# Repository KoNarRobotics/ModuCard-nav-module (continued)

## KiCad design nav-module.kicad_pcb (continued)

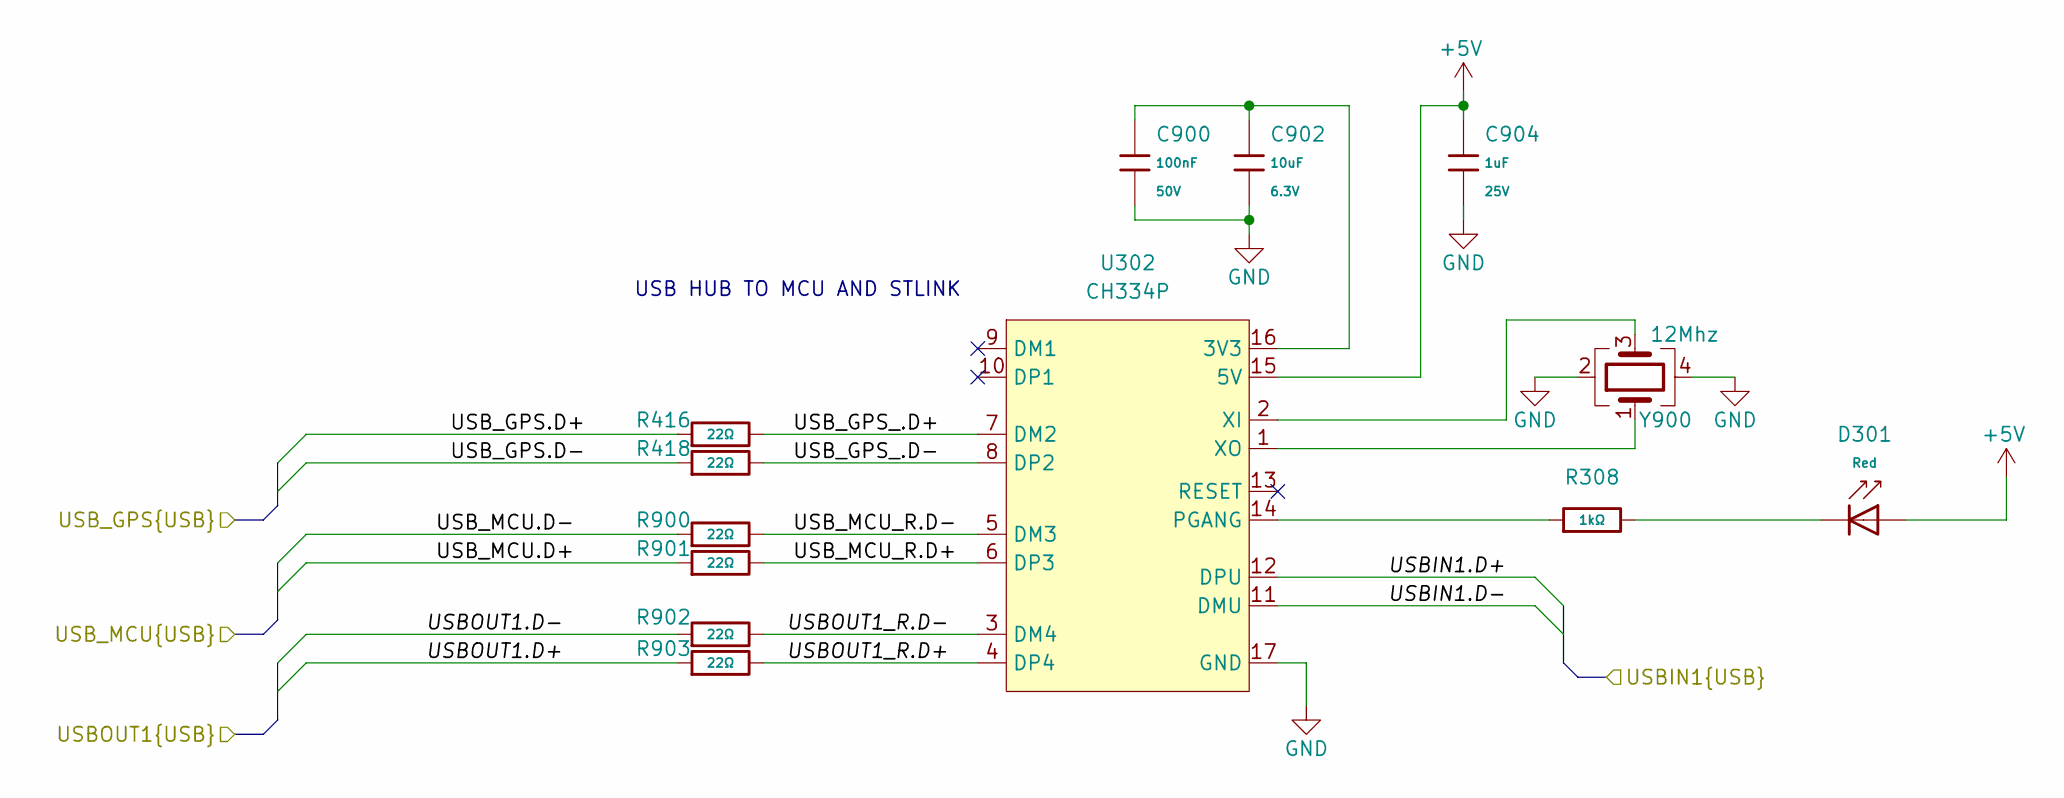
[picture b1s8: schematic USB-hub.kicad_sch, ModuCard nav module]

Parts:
C900: 100nF; C_0402; Voltage Rated 50V; Tolerance ±10%; Part CL05B104KB54PNC; LCSC C307331
C902: 10uF; C_0402; Voltage Rated 6.3V; Tolerance ±20%; Part CL05A106MQ5NUNC; LCSC C15525
C904: 1uF; C_0402; Voltage Rated 25V; Tolerance ±10%; Part CL05A105KA5NQNC; LCSC C52923
D301: Red; D_0603; Part KT-0603R; LCSC C2286
R308: 1kΩ; R_0402; Overload Voltage (Max) 50V; Tolerance ±1%; Part 0402WGF1001TCE; LCSC C11702
R416, R418, R900, R901, R902, R903: 22Ω; R_0402; Overload Voltage (Max) 50V; Tolerance ±1%; Part 0402WGF220JTCE; LCSC C25092
U302: CH334P; QFN-16-1EP_3x3mm_P0.5mm_EP1.7x1.7mm
Y900: 12Mhz; Crystal_SMD_3225-4Pin_3.2x2.5mm

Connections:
+5V: C904.1, D301.2, U302.15 (5V); also elsewhere on the board
/GPS-RTK/USB_GPS.D+: R416.1; also elsewhere on the board
/GPS-RTK/USB_GPS.D-: R418.1; also elsewhere on the board
/MCU/USB_MCU.D+: R901.1; also elsewhere on the board
/MCU/USB_MCU.D-: R900.1; also elsewhere on the board
/ST-LINK/ST-LINK.D+: R903.1; also elsewhere on the board
/ST-LINK/ST-LINK.D-: R902.1; also elsewhere on the board
/USB-hub/USBIN1.D+: U302.12 (DPU); also elsewhere on the board
/USB-hub/USBIN1.D-: U302.11 (DMU); also elsewhere on the board
/USB-hub/USBOUT1_R.D+: R903.2, U302.4 (DP4)
/USB-hub/USBOUT1_R.D-: R902.2, U302.3 (DM4)
/USB-hub/USB_GPS_.D+: R416.2, U302.7 (DM2)
/USB-hub/USB_GPS_.D-: R418.2, U302.8 (DP2)
/USB-hub/USB_MCU_R.D+: R901.2, U302.6 (DP3)
/USB-hub/USB_MCU_R.D-: R900.2, U302.5 (DM3)
GND: C900.2, C902.2, C904.2, U302.17 (GND), Y900.2, Y900.4; also elsewhere on the board
unnamed: D301.1, R308.2
unnamed: C900.1, C902.1, U302.16 (3V3)
unnamed: R308.1, U302.14 (PGANG)
unnamed: U302.2 (XI), Y900.3
unnamed: U302.1 (XO), Y900.1

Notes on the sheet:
USB HUB TO MCU AND STLINK

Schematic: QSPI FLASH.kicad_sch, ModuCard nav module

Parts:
C100: 100nF; C_0402; Voltage Rated 50V; Tolerance ±10%; Part CL05B104KB54PNC; LCSC C307331
U100: W25Q128; SOIC-8_L5.3-W5.3-P1.27-LS8.0-BL; Part W25Q128JVSIQ; LCSC C97521

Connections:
+3V3: C100.1, U100.8 (VCC); also elsewhere on the board
/MCU/QSPI1.CS: U100.1 (CS#); also elsewhere on the board
/MCU/QSPI1.IO0: U100.5 (DI); also elsewhere on the board
/MCU/QSPI1.IO1: U100.2 (DO); also elsewhere on the board
/MCU/QSPI1.IO2: U100.3 (IO2); also elsewhere on the board
/MCU/QSPI1.IO3: U100.7 (IO3); also elsewhere on the board
/MCU/QSPI1.SCLK: U100.6 (CLK); also elsewhere on the board
GND: C100.2, U100.4 (GND); also elsewhere on the board

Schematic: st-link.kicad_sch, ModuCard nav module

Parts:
C700: 1uF; C_0402; Voltage Rated 25V; Tolerance ±10%; Part CL05A105KA5NQNC; LCSC C52923
C701, C702, C703, C704, C705, C706: 100nF; C_0402; Voltage Rated 50V; Tolerance ±10%; Part CL05B104KB54PNC; LCSC C307331
C707, C708: 33pF; C_0402; Voltage Rated 50V; Tolerance ±5%; Part 0402CG330J500NT; LCSC C1562
D700: Blue; D_0603; Part 19-217/BHC-ZL1M2RY/6T; LCSC C2986058
D701: Green; D_0603; Part 19-217/GHC-YR1S2/6T; LCSC C2986059
Q700: MMST3904; Q_SOT-323; Part MMST3904; LCSC C22388837
R700, R702: 100kΩ; R_0402; Overload Voltage (Max) 50V; Tolerance ±1%; Part 0402WGF1003TCE; LCSC C25741
R701, R703, R705, R707, R709, R713: 10kΩ; R_0402; Overload Voltage (Max) 50V; Tolerance ±1%; Part 0402WGF1002TCE; LCSC C25744
R704, R708, R715, R716: 22Ω; R_0402; Overload Voltage (Max) 50V; Tolerance ±1%; Part 0402WGF220JTCE; LCSC C25092
R706: 10kΩ; R_0402; Overload Voltage (Max) 50V; Tolerance ±1%; Part 0402WGF1002TCE; LCSC C25744; not fitted
R710, R714: 100Ω; R_0402; Overload Voltage (Max) 50V; Tolerance ±1%; Part 0402WGF1000TCE; LCSC C25076
R711: 39kΩ; R_0402; Overload Voltage (Max) 50V; Tolerance ±1%; Part 0402WGF3902TCE; LCSC C25783
R712: 1.2kΩ; R_0402; Overload Voltage (Max) 50V; Tolerance ±1%; Part 0402WGF1201TCE; LCSC C25862
TP700, TP701: TestPoint; TestPoint_Pad_D1.0mm
TP702, TP703, TP704, TP705, TP706: TestPoint_Pad_D1.0mm
U700: STM32F103CBTx; LQFP-48_7x7mm_P0.5mm
Y700: 8 MHz; CRYSTAL-SMD_4P-L3.2-W2.5-BL

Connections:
+3V3: C700.1, C701.1, C702.1, C703.1, C704.1, C705.1, Q700.3 (C), R700.1, R701.1, R707.1, TP702.1, U700.1 (VBAT), U700.9 (VDDA), U700.24 (VDD), U700.36 (VDD), U700.48 (VDD); also elsewhere on the board
+5V: R709.1; also elsewhere on the board
/MCU/SWD.SWCLK: R704.2, R715.1; also elsewhere on the board
/MCU/SWD.SWDIO: R716.1; also elsewhere on the board
/MCU/SWD.~RST: R708.1; also elsewhere on the board
/ST-LINK/CLK: TP705.1, U700.37 (PA14)
/ST-LINK/DIO: TP704.1, U700.34 (PA13)
/ST-LINK/LED: D700.1, D701.2, U700.30 (PA9)
/ST-LINK/ST-LINK.D+: R712.2, U700.33 (PA12); also elsewhere on the board
/ST-LINK/ST-LINK.D-: U700.32 (PA11); also elsewhere on the board
/ST-LINK/STLINK-BOOT0: R702.2, TP703.1, U700.44 (BOOT0)
/ST-LINK/STLINK-OSC_IN: C707.1, U700.5 (PD0), Y700.1
/ST-LINK/STLINK-OSC_OUT: C708.1, U700.6 (PD1), Y700.3
/ST-LINK/STLINK-RST: C706.1, R700.2, U700.7 (NRST)
/ST-LINK/STLINK_RX: TP701.1, U700.13 (PA3)
/ST-LINK/STLINK_TX: TP700.1, U700.12 (PA2)
/ST-LINK/SWO: U700.31 (PA10)
/ST-LINK/USB_RENUM: R710.2, U700.38 (PA15)
GND: C700.2, C701.2, C702.2, C703.2, C704.2, C705.2, C706.2, C707.2, C708.2, R702.1, R703.2, R705.1, R706.1, R711.2, R713.2, TP706.1, U700.8 (VSSA), U700.23 (VSS), U700.35 (VSS), U700.47 (VSS), Y700.2, Y700.4; also elsewhere on the board
unnamed: D700.2, R707.2
unnamed: D701.1, R713.1
unnamed: Q700.1 (B), R709.2, R710.1, R711.1
unnamed: Q700.2 (E), R712.1
unnamed: R701.2, R703.1, U700.10 (PA0)
unnamed: R704.1, U700.15 (PA5)
unnamed: R708.2, U700.18 (PB0)
unnamed: R714.2, U700.25 (PB12)
unnamed: R715.2, U700.26 (PB13)
unnamed: R714.1, R716.2, U700.27 (PB14)
unnamed: R705.2, U700.2 (PC13)
unnamed: R706.2, U700.3 (PC14)

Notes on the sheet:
Alternative GD32F103CB
SWD
NOTICE:
C707=C708 = (CL - 4pF) * 2
Monitor voltage rail 3V3 instead of target MCU voltage
https://stm32world.com/wiki/DIY_STM32_Programmer_(ST-Link/V2-1)
CAUTION:
Populate with STM32F103C8, STM32F103CB
Should be 1k5, but we try 1k2 because it is in basic parts
ACTIVITY LED
for providing amazing reverse engeenering of ST-link
MANDATORY CB VERSION
FORCE RENUMERATION OF USB DEVICES
https://github.com/lbthomsen/st-link/tree/master
Credit to:

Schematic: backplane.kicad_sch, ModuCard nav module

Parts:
J200: 09031967921; DIN41612_R_3x32_Female_Horizontal_THT; PARTREV D
U200: PESD5V0S2BT; SOT-23

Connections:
+5V_STDBY: J200.a3, J200.b3, J200.c3
+12V: J200.a11, J200.a12, J200.b11, J200.b12, J200.c11, J200.c12; also elsewhere on the board
+24V: J200.a14, J200.b14, J200.c14
/Backplane/BACKPLANE.D+: J200.a2, U200.2; also elsewhere on the board
/Backplane/BACKPLANE.D-: J200.c2, U200.1; also elsewhere on the board
/Backplane/CAN1.+: J200.a5, J200.b5, J200.c5; also elsewhere on the board
/Backplane/CAN1.-: J200.a6, J200.b6, J200.c6; also elsewhere on the board
/Backplane/CAN2.+: J200.a8, J200.b8, J200.c8; also elsewhere on the board
/Backplane/CAN2.-: J200.a9, J200.b9, J200.c9; also elsewhere on the board
/Backplane/GPIOC0: J200.b16
/Backplane/GPIOC1: J200.b17
/Backplane/GPIOC2: J200.b18
/Backplane/GPIOC3: J200.b19
/Backplane/GPIOC4: J200.b20
/Backplane/GPIOC5: J200.b21
/Backplane/GPIOC6: J200.b22
/Backplane/GPIOC7: J200.b23
/Backplane/GPIOC8: J200.b24
/Backplane/GPIOC9: J200.b25
/Backplane/GPIOC10: J200.b26
/Backplane/GPIOC11: J200.b27
/Backplane/GPIOC12: J200.b28
/Backplane/GPIOC13: J200.b29
/Backplane/GPIOC14: J200.b30
/Backplane/GPIOC15: J200.b31
/Backplane/GPIOL0: J200.a16
/Backplane/GPIOL1: J200.a17
/Backplane/GPIOL2: J200.a18
/Backplane/GPIOL3: J200.a19
/Backplane/GPIOL4: J200.a20
/Backplane/GPIOL5: J200.a21
/Backplane/GPIOL6: J200.a22
/Backplane/GPIOL7: J200.a23
/Backplane/GPIOL8: J200.a24
/Backplane/GPIOL9: J200.a25
/Backplane/GPIOL10: J200.a26
/Backplane/GPIOL11: J200.a27
/Backplane/GPIOL12: J200.a28
/Backplane/GPIOL13: J200.a29
/Backplane/GPIOL14: J200.a30
/Backplane/GPIOL15: J200.a31
/Backplane/GPIOR0: J200.c16
/Backplane/GPIOR1: J200.c17
/Backplane/GPIOR2: J200.c18
/Backplane/GPIOR3: J200.c19
/Backplane/GPIOR4: J200.c20
/Backplane/GPIOR5: J200.c21
/Backplane/GPIOR6: J200.c22
/Backplane/GPIOR7: J200.c23
/Backplane/GPIOR8: J200.c24
/Backplane/GPIOR9: J200.c25
/Backplane/GPIOR10: J200.c26
/Backplane/GPIOR11: J200.c27
/Backplane/GPIOR12: J200.c28
/Backplane/GPIOR13: J200.c29
/Backplane/GPIOR14: J200.c30
/Backplane/GPIOR15: J200.c31
GND: J200.a1, J200.a4, J200.a7, J200.a10, J200.a13, J200.a15, J200.a32, J200.b1, J200.b2, J200.b4, J200.b7, J200.b10, J200.b13, J200.b15, J200.b32, J200.c1, J200.c4, J200.c7, J200.c10, J200.c13, J200.c15, J200.c32, U200.3; also elsewhere on the board

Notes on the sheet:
USB
CAN
POWER FLAGS
USB

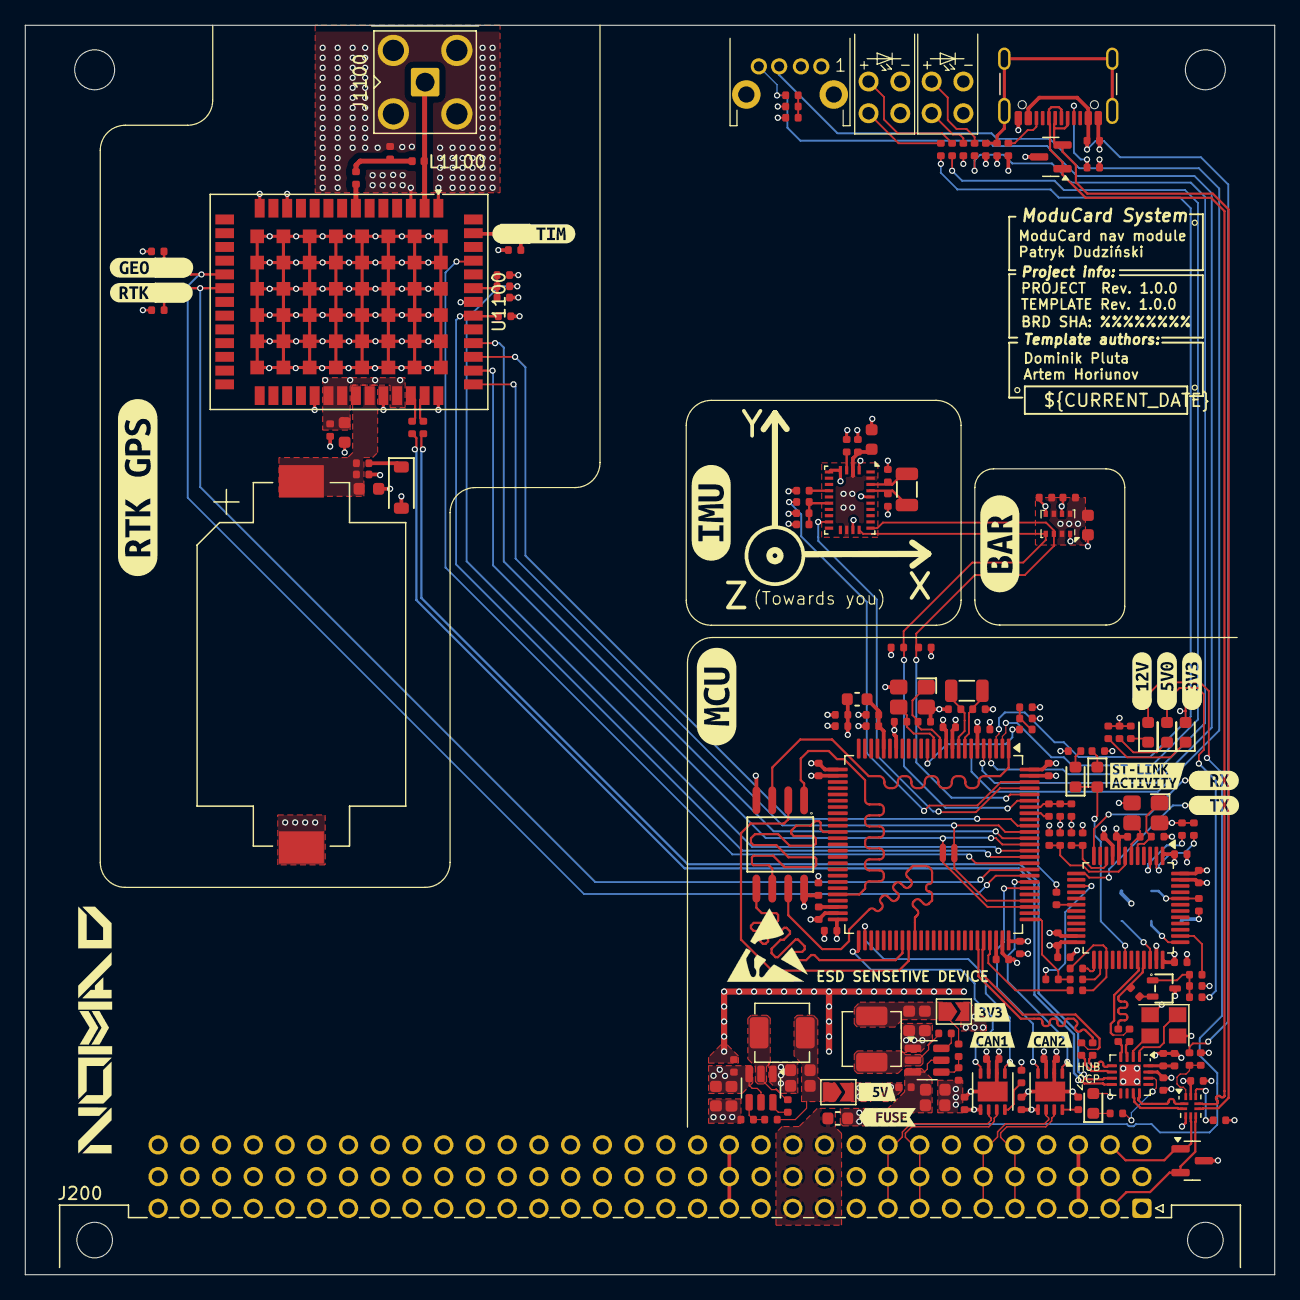
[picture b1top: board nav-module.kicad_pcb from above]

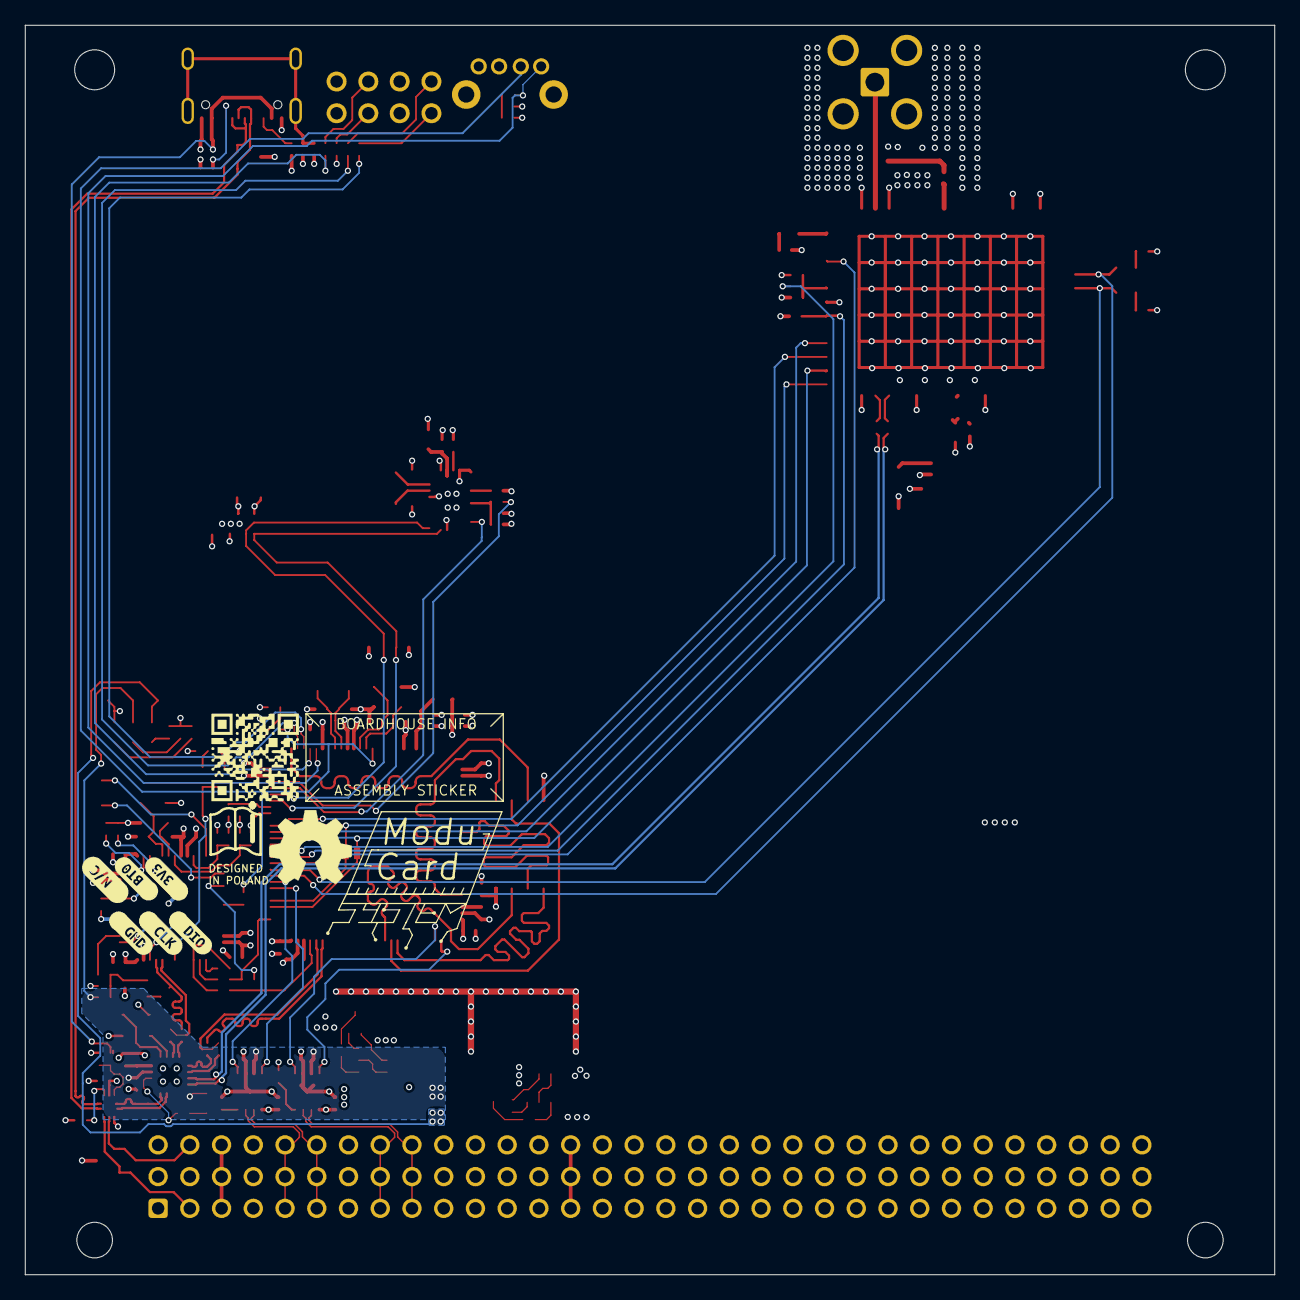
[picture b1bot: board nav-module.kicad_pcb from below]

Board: 4 copper layers, 100.0 x 100.0 mm, 208 parts (11 on the bottom side), 137 nets.

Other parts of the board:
kibuzzard-67B20BD5: G***; kibuzzard-67B20BD5
kibuzzard-67B63E8D: G***; kibuzzard-67B63E8D
kibuzzard-67B69BE3: G***; kibuzzard-67B69BE3
kibuzzard-67B69BEA: G***; kibuzzard-67B69BEA
kibuzzard-67B69D00: G***; kibuzzard-67B69D00
kibuzzard-67B69E2F: G***; kibuzzard-67B69E2F
kibuzzard-67B69E78: G***; kibuzzard-67B69E78
kibuzzard-67B69F23: G***; kibuzzard-67B69F23
kibuzzard-67B219C6: G***; kibuzzard-67B219C6
kibuzzard-67B624A4: G***; kibuzzard-67B624A4
kibuzzard-67B643AC: G***; kibuzzard-67B643AC
kibuzzard-67B643DE: G***; kibuzzard-67B643DE
kibuzzard-67B643EE: G***; kibuzzard-67B643EE
kibuzzard-67B2198C: G***; kibuzzard-67B2198C
kibuzzard-67B6248A: G***; kibuzzard-67B6248A
kibuzzard-67B6249A: G***; kibuzzard-67B6249A
kibuzzard-67B6438D: G***; kibuzzard-67B6438D
kibuzzard-67B37005: G***; kibuzzard-67B37005
kibuzzard-67B37418: G***; kibuzzard-67B37418
kibuzzard-67B37472: G***; kibuzzard-67B37472
kibuzzard-67B62451: G***; kibuzzard-67B62451
kibuzzard-67B62470: G***; kibuzzard-67B62470
kibuzzard-67B62521: G***; kibuzzard-67B62521
kibuzzard-67BE5A95: G***; kibuzzard-67BE5A95

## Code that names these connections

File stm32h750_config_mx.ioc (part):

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Mcu.Name=STM32H750VBTx
Mcu.Package=LQFP100
Mcu.UserName=STM32H750VBTx
PA0.Mode=IN16-Single-Ended
PA0.Signal=ADC1_INP16
PA1.Mode=IN17-Single-Ended
PA1.Signal=ADC1_INP17
PA11.Mode=Device_Only
PA11.Signal=USB_OTG_FS_DM
PA12.Mode=Device_Only
PA12.Signal=USB_OTG_FS_DP
PA13\ (JTMS/SWDIO).Mode=Serial_Wire
PA13\ (JTMS/SWDIO).Signal=DEBUG_JTMS-SWDIO
PA14\ (JTCK/SWCLK).Mode=Serial_Wire
PA14\ (JTCK/SWCLK).Signal=DEBUG_JTCK-SWCLK
PA2.Signal=ADCx_INP14
PA3.Signal=ADCx_INP15
PA4.Signal=COMP_DAC11_group
PA5.Signal=COMP_DAC12_group
PA6.Signal=ADCx_INP3
PA7.Signal=ADCx_INP7
PB0.Signal=ADCx_INP9
PB1.Signal=ADCx_INP5
PB10.Mode=Single Bank 1
PB10.Signal=QUADSPI_BK1_NCS
PB12.Mode=FDCAN_Activate
PB12.Signal=FDCAN2_RX
PB13.Mode=FDCAN_Activate
PB13.Signal=FDCAN2_TX
PB2.Mode=Single Bank 1
PB2.Signal=QUADSPI_CLK
PB3\ (JTDO/TRACESWO).Mode=Full_Duplex_Master
PB3\ (JTDO/TRACESWO).Signal=SPI1_SCK
PB4\ (NJTRST).Mode=Full_Duplex_Master
PB4\ (NJTRST).Signal=SPI1_MISO
PB5.Signal=GPIO_Output
PB7.Signal=GPIO_Output
PB8.Mode=I2C
PB8.Signal=I2C1_SCL
PB9.Mode=I2C
PB9.Signal=I2C1_SDA
PC0.Signal=ADCx_INP10
PC1.Signal=ADCx_INP11
PC10.Mode=Asynchronous
PC10.Signal=UART4_TX
PC11.Mode=Asynchronous
PC11.Signal=UART4_RX
PC14-OSC32_IN\ (OSC32_IN).Mode=LSE-External-Oscillator
PC14-OSC32_IN\ (OSC32_IN).Signal=RCC_OSC32_IN
PC15-OSC32_OUT\ (OSC32_OUT).Mode=LSE-External-Oscillator
PC15-OSC32_OUT\ (OSC32_OUT).Signal=RCC_OSC32_OUT
PC4.Signal=ADCx_INP4
PC5.Signal=ADCx_INP8
PD0.Mode=FDCAN_Activate
PD0.Signal=FDCAN1_RX
PD1.Mode=FDCAN_Activate
PD1.Signal=FDCAN1_TX
PD11.Mode=Single Bank 1
PD11.Signal=QUADSPI_BK1_IO0
PD12.Mode=Single Bank 1
PD12.Signal=QUADSPI_BK1_IO1
PD13.Mode=Single Bank 1
PD13.Signal=QUADSPI_BK1_IO3
PD2.Signal=GPIO_Input
PD3.Signal=GPIO_Input
PD4.Signal=GPXTI4
PD5.Signal=GPIO_Output
PD6.Signal=GPIO_Output
PD7.Mode=Full_Duplex_Master
PD7.Signal=SPI1_MOSI
PE0.Signal=GPXTI0
PE1.Signal=GPIO_Output
PE2.Mode=Single Bank 1
PE2.Signal=QUADSPI_BK1_IO2
PH0-OSC_IN\ (PH0).Mode=HSE-External-Oscillator
PH0-OSC_IN\ (PH0).Signal=RCC_OSC_IN
PH1-OSC_OUT\ (PH1).Mode=HSE-External-Oscillator
PH1-OSC_OUT\ (PH1).Signal=RCC_OSC_OUT
RCC.HSE_VALUE=12000000
RCC.SYSCLKFreq_VALUE=480000000
RCC.SYSCLKSource=RCC_SYSCLKSOURCE_PLLCLK
board=custom

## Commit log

2025-02-20 [rev 1.0] rev 1.0 finished
2025-02-20 [RF gps] update rev 1.1 fixed update rf place
2025-02-21 [3d models] added 3d models for gps and can tranciver
2025-02-22 final check , added pull up resistors on i2c
2025-02-22 Add generated schematic PDF and Gerber files
2025-02-22 added icons on silkscreen
2025-02-26 [barometer] added presure sensor
